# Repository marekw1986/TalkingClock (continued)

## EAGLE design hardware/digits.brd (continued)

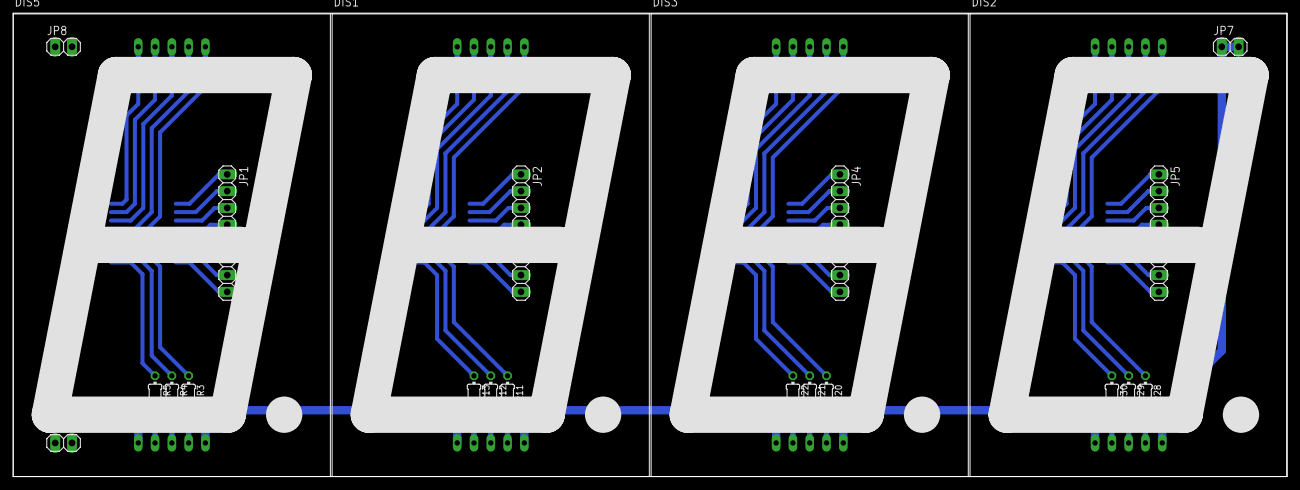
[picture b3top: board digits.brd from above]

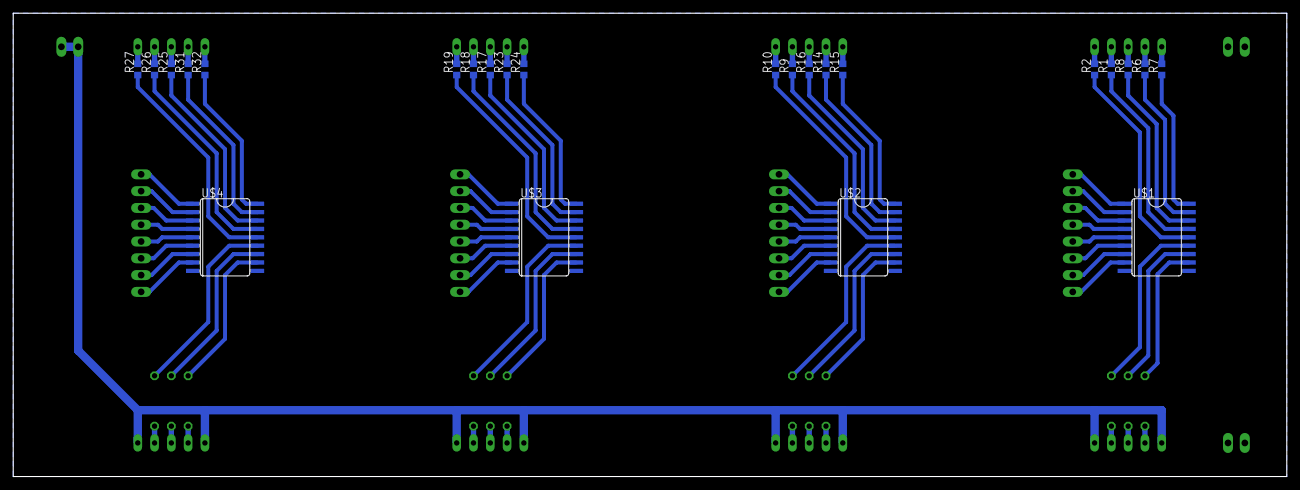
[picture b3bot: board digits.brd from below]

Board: 2 copper layers, 192.7 x 70.1 mm, 47 parts (24 on the bottom side), 98 nets.

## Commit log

2019-05-29 add new files
2019-05-29 minor changes
2020-08-23 major changes
2020-08-23 removed file
2020-08-24 GAL address decoders added
2020-08-27 README.md updated
2020-09-06 SP0256 dictionary added
2020-09-07 It speaks now
2020-09-08 It is throwing oneliners now!
2020-09-08 It throws popcultural references now :)
2020-09-10 DCF77
2020-09-11 some fixes
2020-09-11 fixes
2020-09-11 fastcalls added
2020-09-18 PCB added
2020-09-24 One bug fixed
2020-09-24 Some changes
2020-10-01 Makefile modified
2020-10-05 watchdog handling and Makefile changes
2020-10-08 DCF77 fix
2020-11-18 clear code
2021-03-12 cleaned
2021-03-22 Timers fixed
2021-03-22 Timers and sound
2021-03-25 MC6840 code fixed
2021-03-25 PCB updated
2022-11-07 Debugging DCF77
2022-11-08 DCF77 update
2022-11-08 another DCF update
2022-11-09 DCF77 debug info
2022-11-24 millis() usadge adapted to 12.5 ms systick
2022-11-24 DCF77 adapted to 12.5 ms systick interrupt
2022-11-27 Optimization relading timer every time not needed
2022-11-27 DCF77 printfs disabled
2022-12-02 Option of disabling DCF77
